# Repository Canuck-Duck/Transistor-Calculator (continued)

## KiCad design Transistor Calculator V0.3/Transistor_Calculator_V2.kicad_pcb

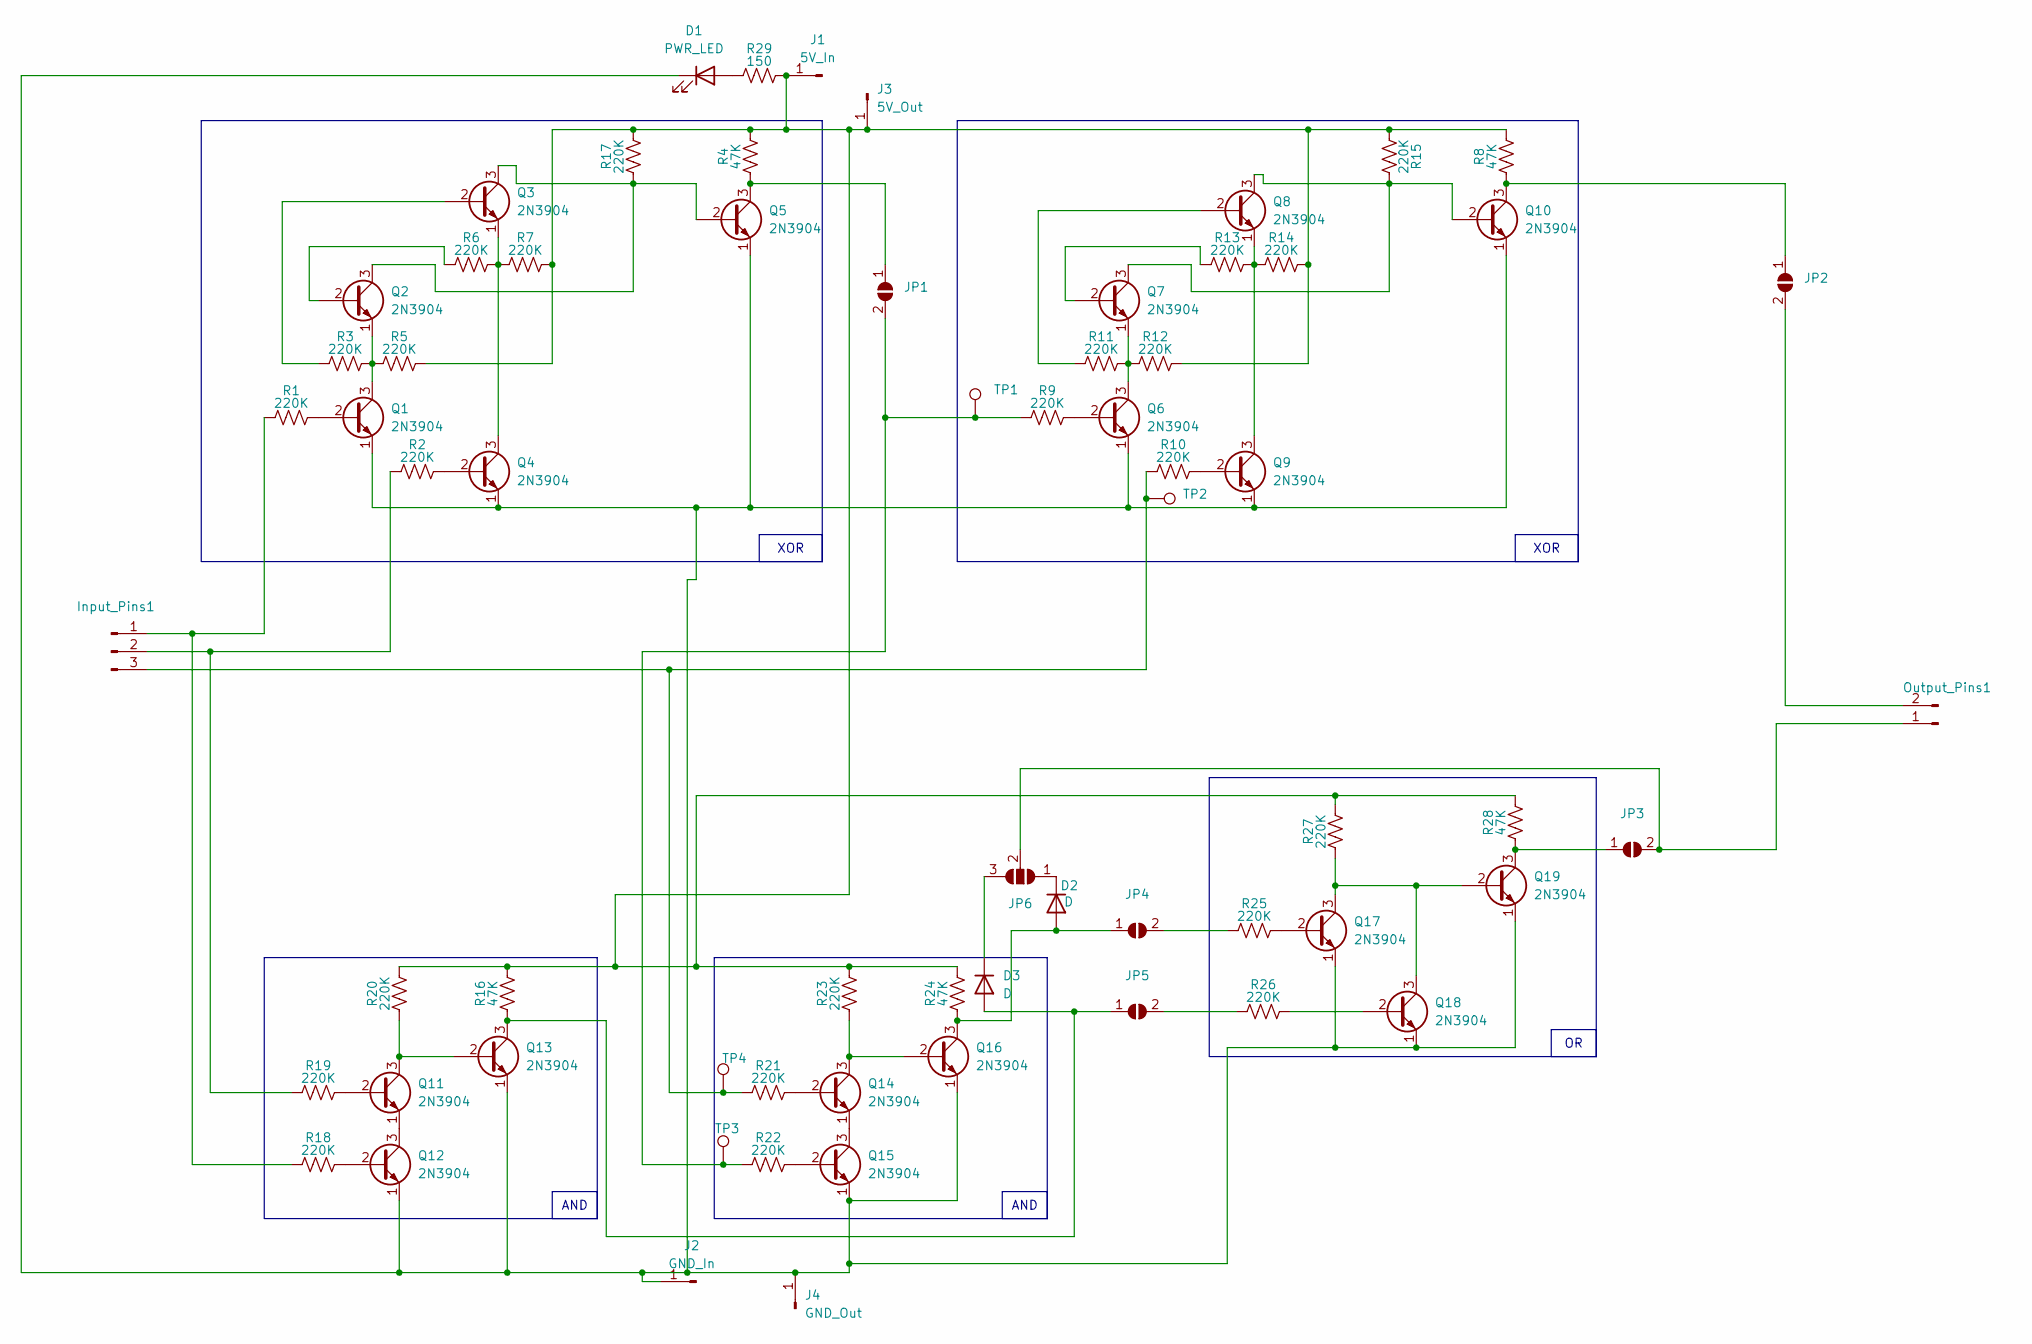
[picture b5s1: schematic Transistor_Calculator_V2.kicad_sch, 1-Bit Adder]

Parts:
D1: PWR_LED; LED_D5.0mm
D2, D3: D; D_A-405_P2.54mm_Vertical_AnodeUp
Input_Pins1: SolderWire-0.5sqmm_1x03_P4.6mm_D0.9mm_OD2.1mm
J1: 5V_In; Pin_D1.0mm_L10.0mm_LooseFit
J2: GND_In; Pin_D1.0mm_L10.0mm_LooseFit
J3: 5V_Out; Pin_D1.0mm_L10.0mm_LooseFit
J4: GND_Out; Pin_D1.0mm_L10.0mm_LooseFit
JP1, JP2, JP3, JP4, JP5: SolderJumper-2_P1.3mm_Open_RoundedPad1.0x1.5mm
JP6: SolderJumper-3_P1.3mm_Open_RoundedPad1.0x1.5mm
Output_Pins1: SolderWire-0.5sqmm_1x02_P4.6mm_D0.9mm_OD2.1mm
Q1, Q2, Q3, Q4, Q5, Q6, Q7, Q8, Q9, Q10, Q11, Q12, Q13, Q14, Q15, Q16, Q17, Q18, Q19: 2N3904; TO-92_HandSolder
R1, R2, R3, R5, R6, R7, R9, R10, R11, R12, R13, R14, R15, R17, R18, R19, R20, R21, R22, R23, R25, R26, R27: 220K; R_Axial_DIN0207_L6.3mm_D2.5mm_P2.54mm_Vertical
R4, R8, R16, R24, R28: 47K; R_Axial_DIN0207_L6.3mm_D2.5mm_P2.54mm_Vertical
R29: 150; R_Axial_DIN0207_L6.3mm_D2.5mm_P2.54mm_Vertical
TP1, TP2, TP3, TP4: TestPoint_Pad_1.0x1.0mm

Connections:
unnamed: D1.2 (A), R29.1
unnamed: D1.1 (K), J2.1, J4.1, Q1.1 (E), Q4.1 (E), Q5.1 (E), Q6.1 (E), Q9.1 (E), Q10.1 (E), Q12.1 (E), Q13.1 (E), Q15.1 (E), Q16.1 (E), Q17.1 (E), Q18.1 (E), Q19.1 (E)
unnamed: D2.2 (A), JP4.1 (A), Q16.3 (C), R24.1
unnamed: D2.1 (K), JP6.1 (A)
unnamed: D3.2 (A), JP5.1 (A), Q13.3 (C), R16.1
unnamed: D3.1 (K), JP6.3 (B)
unnamed: Input_Pins1.1, R1.1, R18.1
unnamed: Input_Pins1.2, R2.1, R19.1
unnamed: Input_Pins1.3, R10.1, R21.1, TP2.1, TP4.1
unnamed: J1.1, J3.1, R4.2, R5.2, R7.2, R8.2, R12.2, R14.2, R15.1, R16.2, R17.2, R20.2, R23.2, R24.2, R27.2, R28.2, R29.2
unnamed: JP1.1 (A), Q5.3 (C), R4.1
unnamed: JP1.2 (B), R9.1, R22.1, TP1.1, TP3.1
unnamed: JP2.1 (A), Q10.3 (C), R8.1
unnamed: JP2.2 (B), Output_Pins1.2
unnamed: JP3.1 (A), Q19.3 (C), R28.1
unnamed: JP3.2 (B), JP6.2 (C), Output_Pins1.1
unnamed: JP4.2 (B), R25.1
unnamed: JP5.2 (B), R26.1
unnamed: Q1.2 (B), R1.2
unnamed: Q1.3 (C), Q2.1 (E), R3.2, R5.1
unnamed: Q2.2 (B), R6.1
unnamed: Q2.3 (C), Q3.3 (C), Q5.2 (B), R17.1
unnamed: Q3.2 (B), R3.1
unnamed: Q3.1 (E), Q4.3 (C), R6.2, R7.1
unnamed: Q4.2 (B), R2.2
unnamed: Q6.2 (B), R9.2
unnamed: Q6.3 (C), Q7.1 (E), R11.2, R12.1
unnamed: Q7.2 (B), R13.1
unnamed: Q8.2 (B), R11.1
unnamed: Q8.1 (E), Q9.3 (C), R13.2, R14.1
unnamed: Q9.2 (B), R10.2
unnamed: Q7.3 (C), Q8.3 (C), Q10.2 (B), R15.2
unnamed: Q11.2 (B), R19.2
unnamed: Q11.3 (C), Q13.2 (B), R20.1
unnamed: Q11.1 (E), Q12.3 (C)
unnamed: Q12.2 (B), R18.2
unnamed: Q14.2 (B), R21.2
unnamed: Q14.3 (C), Q16.2 (B), R23.1
unnamed: Q14.1 (E), Q15.3 (C)
unnamed: Q15.2 (B), R22.2
unnamed: Q17.2 (B), R25.2
unnamed: Q17.3 (C), Q18.3 (C), Q19.2 (B), R27.1
unnamed: Q18.2 (B), R26.2

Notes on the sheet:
XOR
AND

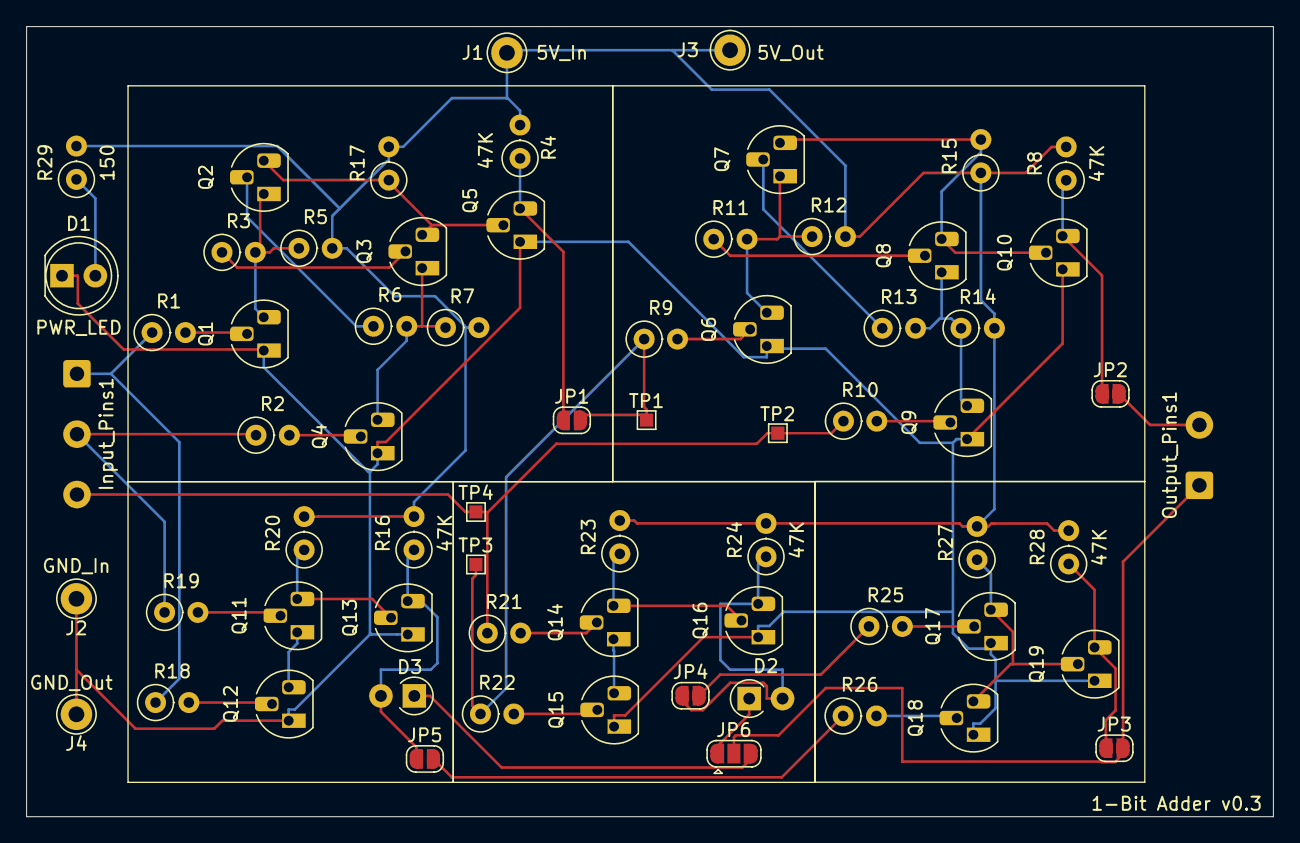
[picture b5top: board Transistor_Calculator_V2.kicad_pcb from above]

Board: 2 copper layers, 95.0 x 60.2 mm, 67 parts (0 on the bottom side), 43 nets.

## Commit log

2025-01-27 Added a common ground with the pico and the EEPROM
2025-02-25 New V2 for 8-bit to BCD
2025-02-26 PCB Layout modification
2025-04-08 Small changes
2025-06-09 Small changes to fix bugs with new update
2025-06-10 New switch board
2025-06-15 Finished Switch Board
2025-06-16 Final changes to BCD V2 and switch board
